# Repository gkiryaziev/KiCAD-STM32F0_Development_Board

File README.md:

## KiCAD-STM32F0_Development_Board

[KiCAD](http://kicad-pcb.org/) [STM32F0](http://www.st.com/en/microcontrollers/stm32f0-series.html?querycriteria=productId=SS1574) Development Board

### Info
```
This board was designed for STM32F103K6T6 microcontroller and for other pin-to-pin compatible.
This is an early version of the board and is distributed as is.
The missing 3D models you can find on open resources on the Internet.
```

#### License
```
CC BY 4.0
```

### Screenshot

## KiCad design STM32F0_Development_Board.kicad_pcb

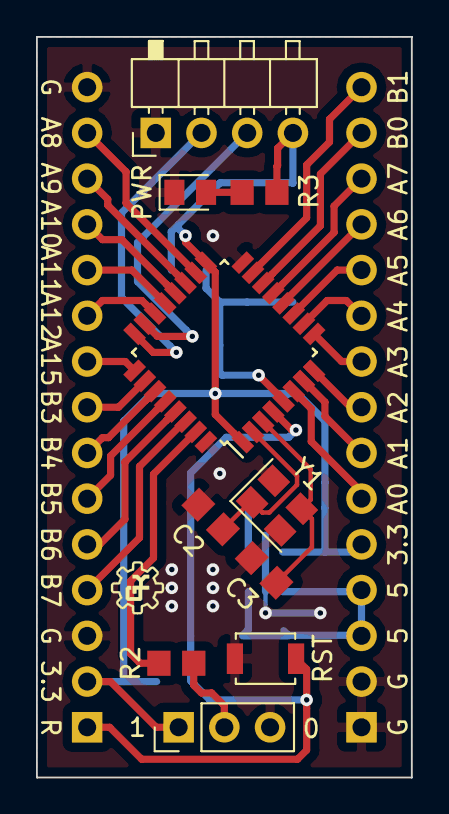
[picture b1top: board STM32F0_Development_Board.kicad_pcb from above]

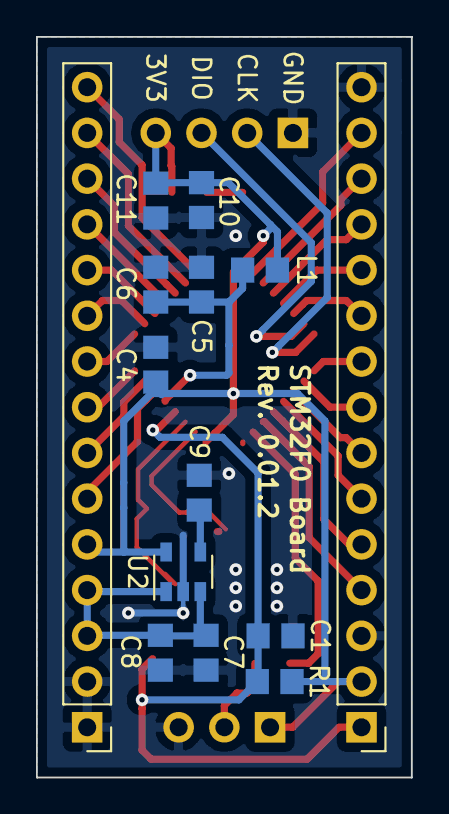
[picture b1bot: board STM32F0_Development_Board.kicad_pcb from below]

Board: 2 copper layers, 20.8 x 41.1 mm, 24 parts (14 on the bottom side), 34 nets.

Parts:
C1, C4, C7, C9, C11: 0.1uF; C_0805_2012Metric_Pad1.29x1.40mm_HandSolder
C2, C3: 18pF; C_0805_2012Metric_Pad1.29x1.40mm_HandSolder
C5: 1uF; C_0805_2012Metric_Pad1.29x1.40mm_HandSolder
C6: 0.01uF; C_0805_2012Metric_Pad1.29x1.40mm_HandSolder
C8, C10: 10uF; C_0805_2012Metric_Pad1.29x1.40mm_HandSolder
D1: PWR; LED_0805_2012Metric_Pad1.12x1.40mm_HandSolder
J1, J2: Conn_01x15; PinHeader_1x15_P2.54mm_Vertical
J3: SWD; PinHeader_1x04_P2.54mm_Horizontal_Short
J4: BOOT; PinHeader_1x03_P2.54mm_Vertical
L1: 10uH; L_0805_2012Metric_Pad1.29x1.40mm_HandSolder
R1, R2: 10k; R_0805_2012Metric_Pad1.29x1.40mm_HandSolder
R3: 470R; R_0805_2012Metric_Pad1.29x1.40mm_HandSolder
SW1: RESET; SW_SPST_B3U-1000P
U1: STM32F051K6Tx; LQFP-32_7x7mm_P0.8mm
U2: MIC5219-3.3; SOT-23-5
Y1: 16Mhz; Crystal_SMD_3225-4Pin_3.2x2.5mm

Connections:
+3V3: C4.2, C10.2, C11.2, J1.2, J2.5, J3.4, J4.1, L1.2, R1.2, R3.2, U1.1, U1.17, U2.5
+5V: C7.2, C8.2, J2.3, J2.4, U2.1, U2.3
/BOOT0: R2.1, U1.31
/NRST: C1.2, J1.1, R1.1, SW1.1, U1.4
/PA0: J2.6, U1.6
/PA1: J2.7, U1.7
/PA2: J2.8, U1.8
/PA3: J2.9, U1.9
/PA4: J2.10, U1.10
/PA5: J2.11, U1.11
/PA6: J2.12, U1.12
/PA7: J2.13, U1.13
/PA8: J1.14, U1.18
/PA9: J1.13, U1.19
/PA10: J1.12, U1.20
/PA11: J1.11, U1.21
/PA12: J1.10, U1.22
/PA15: J1.9, U1.25
/PB0: J2.14, U1.14
/PB1: J2.15, U1.15
/PB3: J1.8, U1.26
/PB4: J1.7, U1.27
/PB5: J1.6, U1.28
/PB6: J1.5, U1.29
/PB7: J1.4, U1.30
/PF0: C2.1, U1.2, Y1.1
/PF1: C3.1, U1.3, Y1.3
/SWCLK: J3.2, U1.24
/SWDIO: J3.3, U1.23
/VDDA: C5.2, C6.2, L1.1, U1.5
GND: C1.1, C2.2, C3.2, C4.1, C5.1, C6.1, C7.1, C8.1, C9.1, C10.1, C11.1, D1.1, J1.3, J1.15, J2.1, J2.2, J3.1, J4.3, SW1.2, U1.16, U1.32, U2.2, Y1.2, Y1.4
unnamed: C9.2, U2.4
unnamed: D1.2, R3.1
unnamed: J4.2, R2.2
